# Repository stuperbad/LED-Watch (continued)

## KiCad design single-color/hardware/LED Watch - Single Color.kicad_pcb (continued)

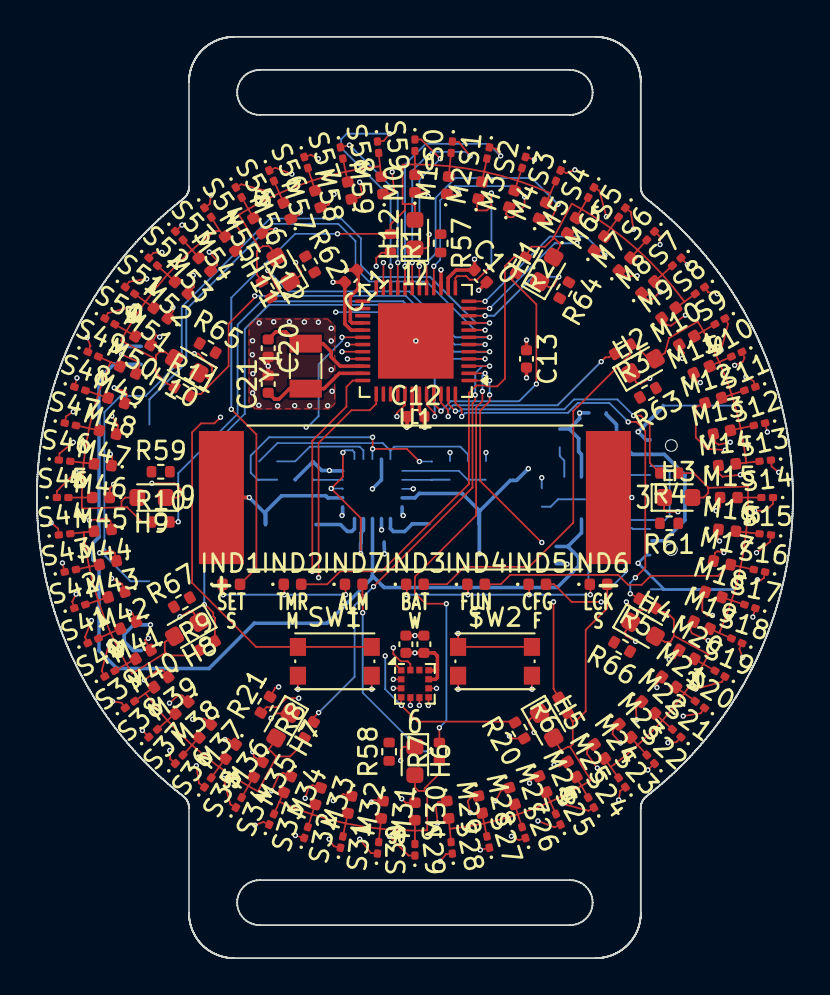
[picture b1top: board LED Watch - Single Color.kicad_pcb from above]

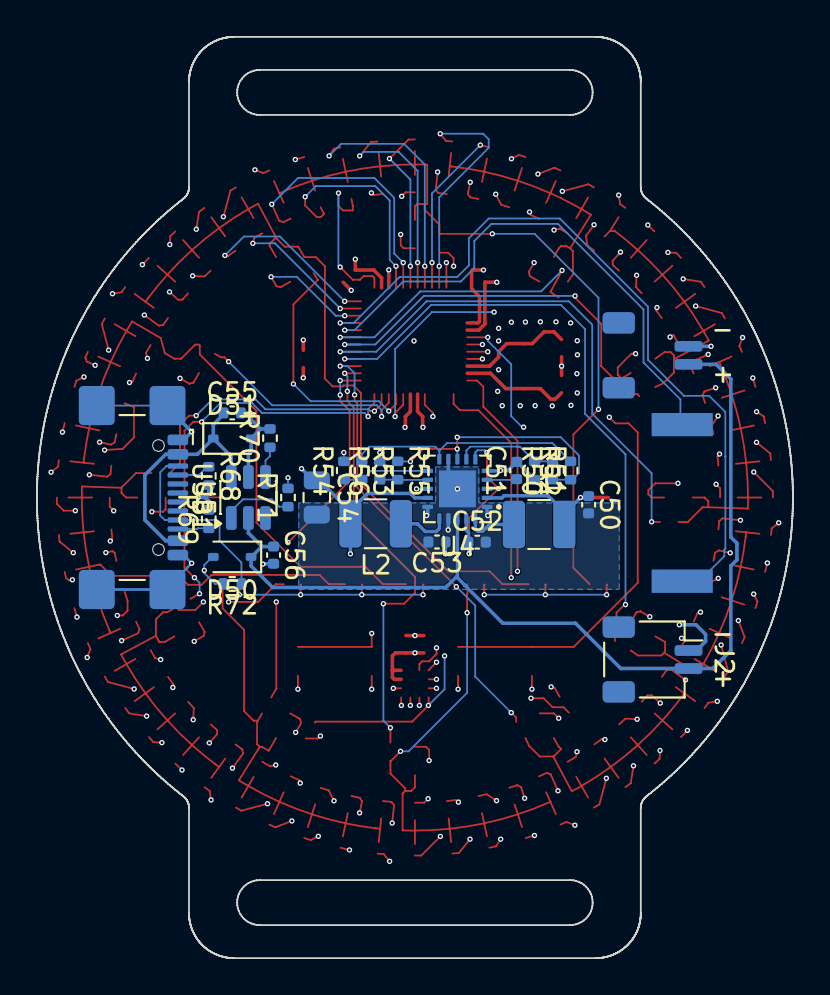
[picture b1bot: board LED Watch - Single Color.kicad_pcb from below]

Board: 4 copper layers, 42.0 x 51.2 mm, 208 parts (31 on the bottom side), 66 nets.

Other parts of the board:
MECH2: LiPo 501515 15x15x5 mm (upper); MECH_LiPo_501515_15x15x5mm
MECH3: LiPo 501515 15x15x5 mm (lower); MECH_LiPo_501515_15x15x5mm

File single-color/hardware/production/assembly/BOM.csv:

Comment,Designator,Footprint,LCSC Part #
PKMCS0909E4000-R1,BZ1,Piezo_Murata_PKMCS0909E4000-R1_9x9mm,C910763
4u7,"C50,C52",C_0402_1005Metric,C23733
10n,"C51,C53",C_0402_1005Metric,C15195
22u,C54,C_0805_2012Metric,C109314
1u,"C55,C56",C_0402_1005Metric,C52923
BAT54WS,D50,D_SOD-323,C304155
UDD32C05L01,D51,D_SOD-323,C19185929
LiPo,"J1,J1B",JST_SH_SM02B-SRSS-TB_1x02-1MP_P1.00mm_Horizontal,C160402
USB-C power + UPDI (GCT USB4110),J2,USB_C_Receptacle_GCT_USB4110,C5143397
22uH,L1,L_1210_3225Metric,C90320
10uH,L2,L_1210_3225Metric,C74563
6.49M,"R50,R53",R_0402_1005Metric,C172111
5.11M,R51,R_0402_1005Metric,C166448
1.47M,R52,R_0402_1005Metric,C477211
3.74M,R54,R_0402_1005Metric,C477705
7.32M,R55,R_0402_1005Metric,C423137
4.22M,R56,R_0402_1005Metric,C423173
5.1k,"R68,R69",R_0402_1005Metric,C25905
10k,"R20,R21,R57,R58,R59,R61,R62,R63,R64,R65,R66,R67,R70,R71",R_0402_1005Metric,C25744
1k,R72,R_0402_1005Metric,C11702
BQ25570RGRR,U4,BQ25570RGR_VQFN-20_3.5x3.5mm_P0.5mm_EP2.05mm,C506250
BQ21040DBV,U5,SOT-23-6,C202311
100n,"C10,C11,C12,C30,C31",C_0402_1005Metric,C1525
10u,C13,C_0402_1005Metric,C15525
18p,"C20,C21",C_0402_1005Metric,C106202
LED white 0603,"H1,H10,H11,H12,H2,H3,H4,H5,H6,H7,H8,H9",LED_0603_1608Metric,C2290
LED white 0402,"IND1,IND2,IND3,IND4,IND5,IND6,IND7,M0,M1,M10,M11,M12,M13,M14,M15,M16,M17,M18,M19,M2,M20,M21,M22,M23,M24,M25,M26,M27,M28,M29,M3,M30,M31,M32,M33,M34,M35,M36,M37,M38,M39,M4,M40,M41,M42,M43,M44,M45,M46,M47,M48,M49,M5,M50,M51,M52,M53,M54,M55,M56,M57,M58,M59,M6,M7,M8,M9",LED_0402_1005Metric,C20613596
220,"R1,R10,R11,R12,R2,R3,R4,R5,R6,R7,R8,R9",R_0402_1005Metric,C25091
LED white 0201,"S0,S1,S10,S11,S12,S13,S14,S15,S16,S17,S18,S19,S2,S20,S21,S22,S23,S24,S25,S26,S27,S28,S29,S3,S30,S31,S32,S33,S34,S35,S36,S37,S38,S39,S4,S40,S41,S42,S43,S44,S45,S46,S47,S48,S49,S5,S50,S51,S52,S53,S54,S55,S56,S57,S58,S59,S6,S7,S8,S9",LED_0201_0603Metric,C965789
SW_Push,"SW1,SW2",SW_Push_1P1T_NO_CK_KMR2,C72443
AVR128DB48-I/6LX,U1,QFN-48-1EP_6x6mm_P0.4mm_EP4.2x4.2mm,C1019768
LIS2DW12TR,U2,LGA-12_2x2mm_P0.5mm,C189624
32.768kHz,Y1,Crystal_SMD_3215-2Pin_3.2x1.5mm,C97606

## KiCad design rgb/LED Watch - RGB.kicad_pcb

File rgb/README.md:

# LED Watch - RGB

The RGB watch: 132 RGB LEDs on three rings plus 7 RGB mode lights, JLCPCB-assemblable parts, AVR128DB64, solar harvester, two LiPo cells, buzzer, accelerometer and buttons. **Status (2026-10-15): placement sketch only**, no schematic, nothing routed. Open **`LED Watch - RGB.kicad_pro`** (it opens the board; the ring LED pads carry the row and colour nets, nothing else has nets yet).

Read **`docs/DESIGN-SKETCH.md`** first: board size, what goes where, the LED choice and its brightness warning, how the matrix is driven, risks and next steps.

| File / folder | What it is |
|---|---|
| `LED Watch - RGB.kicad_pro` / `.kicad_pcb` | the sketch: 44 mm round board with strap lugs, 132 + 7 LEDs, everything placed on the front and back |
| `docs/` | `DESIGN-SKETCH.md`, `pin-plan.csv` (AVR128DB64 pins), `BOM-candidates.csv` (new parts with LCSC numbers and stock, 2026-10-15) |
| `footprints/LEDWatchRGB.pretty` | the new common-anode LED footprint (fits Nationstar NCD0808RGB1 and Meihua MHPA0808RGBDT) |
| `data/` | `led_matrix.csv` (which LED is which second/minute/hour, row and column), `old_ring.json` (ring data read from the old board) |
| `tools/` | `build_sketch.py` makes the board (KiCad's Python: `"C:\Program Files\KiCad.0in\python.exe" toolsuild_sketch.py`), `extract_old_ring.py`, `check_pad_corners.py` |
| `renders/` | `top.png` (front) and `bottom.png` (back, seen from behind) |
| `mechanical/` | watch outline drawings (SVG), the 3D print and the Rhino layout, all of the **old 43 mm board**; not yet updated |
| `archive/` | **`2026-10-14 old RGB board - routed, Harvatek LEDs, ATmega165PA/`**: the previous RGB project (schematic, fully routed board, project, its Gerbers and the October 2026 fab quote work incl. `OPEN-ISSUES.md` and `jlc-alternatives.md`, and the ring placement script); everything older is in `pre-claude/` |

Below: Evan's original notes (part links and ideas).

---

# LED-Watch
first schematic progress commit. adding RGB sketch schematic as well as
completed single LED ring sketch. need to add buttons and sort out AND
gates in the RGB sketch.
Product Ideas.. data sheets and store locations:

Digikey working parts list: https://www.digikey.com/en/mylists/list/WPRJ7CQ35H

Boards options 

27 i/o pins and in the current sketch: https://www.digikey.com/en/products/detail/microchip-technology/ATMEGA4808-MUR/10444956

32 i/o pins: https://www.digikey.com/en/products/detail/microchip-technology/ATMEGA1284P-MU/1914520

LEDs options

addressable 1mm RGB: 
https://www.sparkfun.com/smd-led-addressable-rgb-apa-104-1010-pack-of-20.html
datasheet: https://cdn.sparkfun.com/assets/3/c/c/0/9/SparkFun_APA-104-1010__5mA__LED_Datasheet.pdf

nonaddressable 1mm RGB: 
https://www.digikey.com/en/products/detail/harvatek-corporation/B36J3RGB-F6C0001H4U1930/13588748

discrete white 0603:
https://www.digikey.com/en/products/detail/everlight-electronics-co-ltd/CSP0603AN101-WP30300563001-3T/15286660?s=N4IgjCBcoMwOxVAYygMwIYBsDOBTANCAPZQDaIALAExgAMAHLSALqEAOALlCAMocBOASwB2AcxABfQhQBsiECkgYcBYmRAy4tWgFYYLdl0i8BI8RKkgq6gASZcAExYSgA

Button Options

19 cent 3.4mm square: https://www.digikey.com/en/products/detail/same-sky-formerly-cui-devices/TS21-34-035-BK-260-SMT-TR/21186457

8 cent 5.2mm square: https://www.digikey.com/en/products/detail/c-k/G01008829/16500348

Battery Parts:

Lipo Connector 
Thru-hole - 2mm.. they make 1mm mb? 
https://www.digikey.com/en/products/detail/jst-sales-america-inc/B2B-PH-K-S/926611

Coin Cell Harness
20mm dia. 3.
Do i need a negative connector? is SMD okay?
https://www.digikey.com/en/products/detail/keystone-electronics/3034TR/4499408

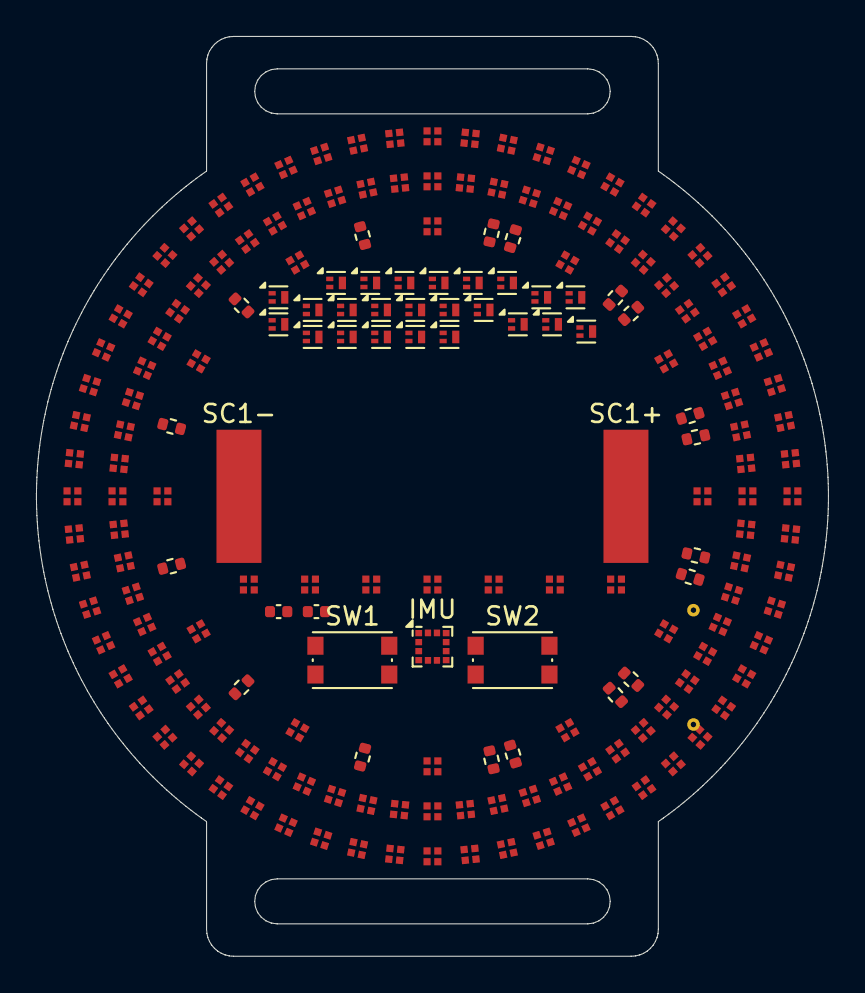
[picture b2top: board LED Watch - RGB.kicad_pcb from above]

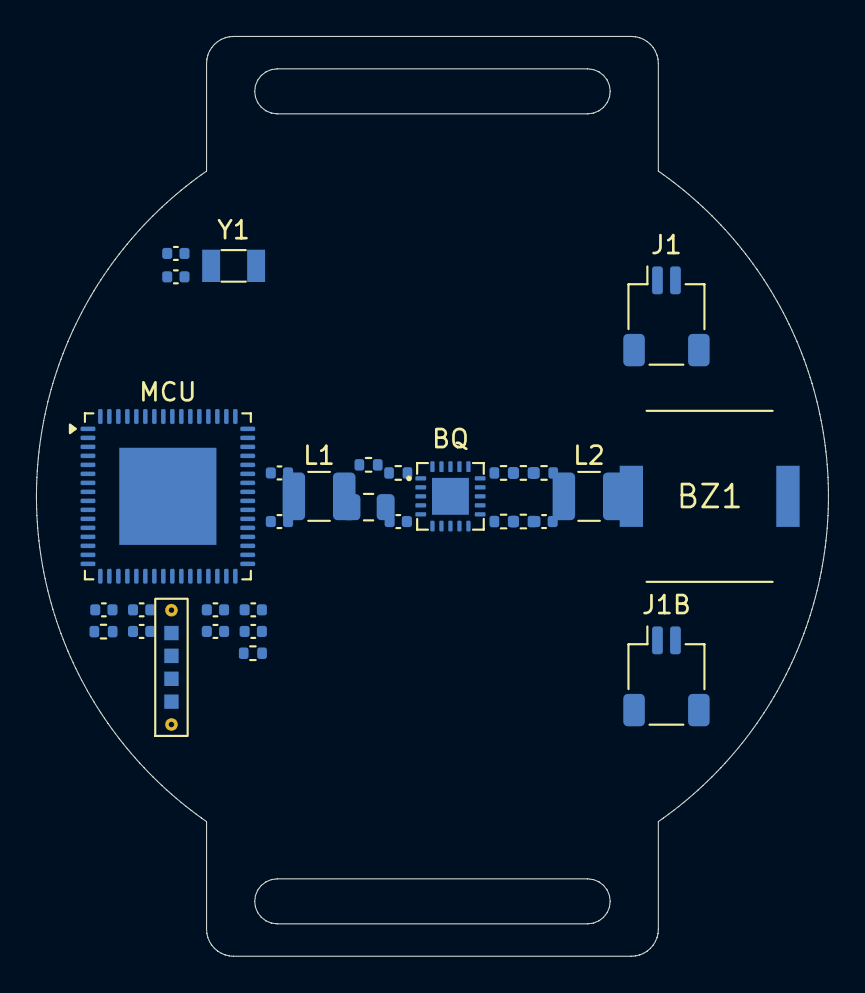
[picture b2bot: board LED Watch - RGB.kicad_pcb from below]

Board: 4 copper layers, 44.0 x 51.1 mm, 220 parts (32 on the bottom side), 40 nets, no tracks yet.

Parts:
BQ: BQ25570; BQ25570RGR_VQFN-20_3.5x3.5mm_P0.5mm_EP2.05mm
BZ1: PKMCS0909E4000-R1; Piezo_Murata_PKMCS0909E4000-R1_9x9mm
C20, C21: 18p; C_0402_1005Metric
C30, C31: 100n; C_0402_1005Metric
C50, C52: 4u7; C_0402_1005Metric
C51, C53: 10n; C_0402_1005Metric
C54: 22u; C_0805_2012Metric
CM1, CM2, CM3, CM4, CM5, CM6, CM7: 100n; C_0402_1005Metric
IMU: LIS2DW12; LGA-12_2x2mm_P0.5mm
IND1, IND2, IND3, IND4, IND5, IND6, IND7: NCD0808RGB1 / MHPA0808RGBDT; RGB0808_CommonAnode
J1, J1B: LiPo; JST_SH_SM02B-SRSS-TB_1x02-1MP_P1.00mm_Horizontal
J2: UPDI pogo; UPDI_Pogo_1x4_P1.27mm_2Guide
L1: 22uH; L_1210_3225Metric
L2: 10uH; L_1210_3225Metric
MCU: AVR128DB64-I/MR; VQFN-64-1EP_9x9mm_P0.5mm_EP5.4x5.4mm
Q1, Q2, Q3, Q4, Q5, Q6, Q7, Q8, Q9, Q10, Q11, Q12, Q13, Q14, Q15, Q16, Q17, Q18, Q19, Q20, Q21, Q22, Q23, Q24: DMP21D0UFB4; Diodes_DFN1006-3
R20, R21: 10k; R_0402_1005Metric
R50, R53, R55: 6.49M; R_0402_1005Metric
R51: 5.11M; R_0402_1005Metric
R52: 1.47M; R_0402_1005Metric
R54, R56: 3.74M; R_0402_1005Metric
RC1, RC2, RC3, RC4, RC5, RC6, RC7, RC8, RC9, RC10, RC11, RC12, RC13, RC14, RC15, RC16, RC17, RC18: R; R_0402_1005Metric
SC1+, SC1-: cell pad; KXOB25_cell_pad_2.5x7.4mm
SW1, SW2: SW; SW_Push_1P1T_NO_CK_KMR2
U2, U3, U4, U5, U6, U7, U8, U9, U10, U11, U12, U13, U14, U15, U16, U17, U18, U19, U20, U21, U22, U23, U24, U25, U26, U27, U28, U29, U30, U31, U32, U33, U34, U35, U36, U37, U38, U39, U40, U41, U42, U43, U44, U45, U46, U47, U48, U49, U50, U51, U52, U53, U54, U55, U56, U57, U58, U59, U60, U61, U62, U63, U64, U65, U66, U67, U68, U69, U70, U71, U72, U73, U74, U75, U76, U77, U78, U79, U80, U81, U82, U83, U84, U85, U86, U87, U88, U89, U90, U91, U92, U93, U94, U95, U96, U97, U98, U99, U100, U101, U102, U103, U104, U105, U106, U107, U108, U109, U110, U111, U112, U113, U114, U115, U116, U117, U118, U119, U120, U121, U122, U123, U124, U125, U126, U127, U128, U129, U130, U131, U132, U133: NCD0808RGB1 / MHPA0808RGBDT; RGB0808_CommonAnode
Y1: 32.768kHz; Crystal_SMD_3215-2Pin_3.2x1.5mm

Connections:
/B1: U2.4, U8.4, U14.4, U20.4, U26.4, U32.4, U38.4, U44.4, U50.4, U56.4, U62.4, U68.4, U74.4, U80.4, U86.4, U92.4, U98.4, U104.4, U110.4, U116.4, U122.4, U128.4
/B2: U3.4, U9.4, U15.4, U21.4, U27.4, U33.4, U39.4, U45.4, U51.4, U57.4, U63.4, U69.4, U75.4, U81.4, U87.4, U93.4, U99.4, U105.4, U111.4, U117.4, U123.4, U129.4
/B3: U4.4, U10.4, U16.4, U22.4, U28.4, U34.4, U40.4, U46.4, U52.4, U58.4, U64.4, U70.4, U76.4, U82.4, U88.4, U94.4, U100.4, U106.4, U112.4, U118.4, U124.4, U130.4
/B4: U5.4, U11.4, U17.4, U23.4, U29.4, U35.4, U41.4, U47.4, U53.4, U59.4, U65.4, U71.4, U77.4, U83.4, U89.4, U95.4, U101.4, U107.4, U113.4, U119.4, U125.4, U131.4
/B5: U6.4, U12.4, U18.4, U24.4, U30.4, U36.4, U42.4, U48.4, U54.4, U60.4, U66.4, U72.4, U78.4, U84.4, U90.4, U96.4, U102.4, U108.4, U114.4, U120.4, U126.4, U132.4
/B6: U7.4, U13.4, U19.4, U25.4, U31.4, U37.4, U43.4, U49.4, U55.4, U61.4, U67.4, U73.4, U79.4, U85.4, U91.4, U97.4, U103.4, U109.4, U115.4, U121.4, U127.4, U133.4
/G1: U2.3, U8.3, U14.3, U20.3, U26.3, U32.3, U38.3, U44.3, U50.3, U56.3, U62.3, U68.3, U74.3, U80.3, U86.3, U92.3, U98.3, U104.3, U110.3, U116.3, U122.3, U128.3
/G2: U3.3, U9.3, U15.3, U21.3, U27.3, U33.3, U39.3, U45.3, U51.3, U57.3, U63.3, U69.3, U75.3, U81.3, U87.3, U93.3, U99.3, U105.3, U111.3, U117.3, U123.3, U129.3
/G3: U4.3, U10.3, U16.3, U22.3, U28.3, U34.3, U40.3, U46.3, U52.3, U58.3, U64.3, U70.3, U76.3, U82.3, U88.3, U94.3, U100.3, U106.3, U112.3, U118.3, U124.3, U130.3
/G4: U5.3, U11.3, U17.3, U23.3, U29.3, U35.3, U41.3, U47.3, U53.3, U59.3, U65.3, U71.3, U77.3, U83.3, U89.3, U95.3, U101.3, U107.3, U113.3, U119.3, U125.3, U131.3
/G5: U6.3, U12.3, U18.3, U24.3, U30.3, U36.3, U42.3, U48.3, U54.3, U60.3, U66.3, U72.3, U78.3, U84.3, U90.3, U96.3, U102.3, U108.3, U114.3, U120.3, U126.3, U132.3
/G6: U7.3, U13.3, U19.3, U25.3, U31.3, U37.3, U43.3, U49.3, U55.3, U61.3, U67.3, U73.3, U79.3, U85.3, U91.3, U97.3, U103.3, U109.3, U115.3, U121.3, U127.3, U133.3
/Hour1: U2.1, U3.1, U4.1, U5.1, U6.1, U7.1
/Hour2: U8.1, U9.1, U10.1, U11.1, U12.1, U13.1
/Minute1: U14.1, U15.1, U16.1, U17.1, U18.1, U19.1
/Minute2: U20.1, U21.1, U22.1, U23.1, U24.1, U25.1
/Minute3: U26.1, U27.1, U28.1, U29.1, U30.1, U31.1
/Minute4: U32.1, U33.1, U34.1, U35.1, U36.1, U37.1
/Minute5: U38.1, U39.1, U40.1, U41.1, U42.1, U43.1
/Minute6: U44.1, U45.1, U46.1, U47.1, U48.1, U49.1
/Minute7: U50.1, U51.1, U52.1, U53.1, U54.1, U55.1
/Minute8: U56.1, U57.1, U58.1, U59.1, U60.1, U61.1
/Minute9: U62.1, U63.1, U64.1, U65.1, U66.1, U67.1
/Minute10: U68.1, U69.1, U70.1, U71.1, U72.1, U73.1
/R1: U2.2, U8.2, U14.2, U20.2, U26.2, U32.2, U38.2, U44.2, U50.2, U56.2, U62.2, U68.2, U74.2, U80.2, U86.2, U92.2, U98.2, U104.2, U110.2, U116.2, U122.2, U128.2
/R2: U3.2, U9.2, U15.2, U21.2, U27.2, U33.2, U39.2, U45.2, U51.2, U57.2, U63.2, U69.2, U75.2, U81.2, U87.2, U93.2, U99.2, U105.2, U111.2, U117.2, U123.2, U129.2
/R3: U4.2, U10.2, U16.2, U22.2, U28.2, U34.2, U40.2, U46.2, U52.2, U58.2, U64.2, U70.2, U76.2, U82.2, U88.2, U94.2, U100.2, U106.2, U112.2, U118.2, U124.2, U130.2
/R4: U5.2, U11.2, U17.2, U23.2, U29.2, U35.2, U41.2, U47.2, U53.2, U59.2, U65.2, U71.2, U77.2, U83.2, U89.2, U95.2, U101.2, U107.2, U113.2, U119.2, U125.2, U131.2
/R5: U6.2, U12.2, U18.2, U24.2, U30.2, U36.2, U42.2, U48.2, U54.2, U60.2, U66.2, U72.2, U78.2, U84.2, U90.2, U96.2, U102.2, U108.2, U114.2, U120.2, U126.2, U132.2
/R6: U7.2, U13.2, U19.2, U25.2, U31.2, U37.2, U43.2, U49.2, U55.2, U61.2, U67.2, U73.2, U79.2, U85.2, U91.2, U97.2, U103.2, U109.2, U115.2, U121.2, U127.2, U133.2
/Second1: U74.1, U75.1, U76.1, U77.1, U78.1, U79.1
/Second2: U80.1, U81.1, U82.1, U83.1, U84.1, U85.1
/Second3: U86.1, U87.1, U88.1, U89.1, U90.1, U91.1
/Second4: U92.1, U93.1, U94.1, U95.1, U96.1, U97.1
/Second5: U98.1, U99.1, U100.1, U101.1, U102.1, U103.1
/Second6: U104.1, U105.1, U106.1, U107.1, U108.1, U109.1
/Second7: U110.1, U111.1, U112.1, U113.1, U114.1, U115.1
/Second8: U116.1, U117.1, U118.1, U119.1, U120.1, U121.1
/Second9: U122.1, U123.1, U124.1, U125.1, U126.1, U127.1
/Second10: U128.1, U129.1, U130.1, U131.1, U132.1, U133.1

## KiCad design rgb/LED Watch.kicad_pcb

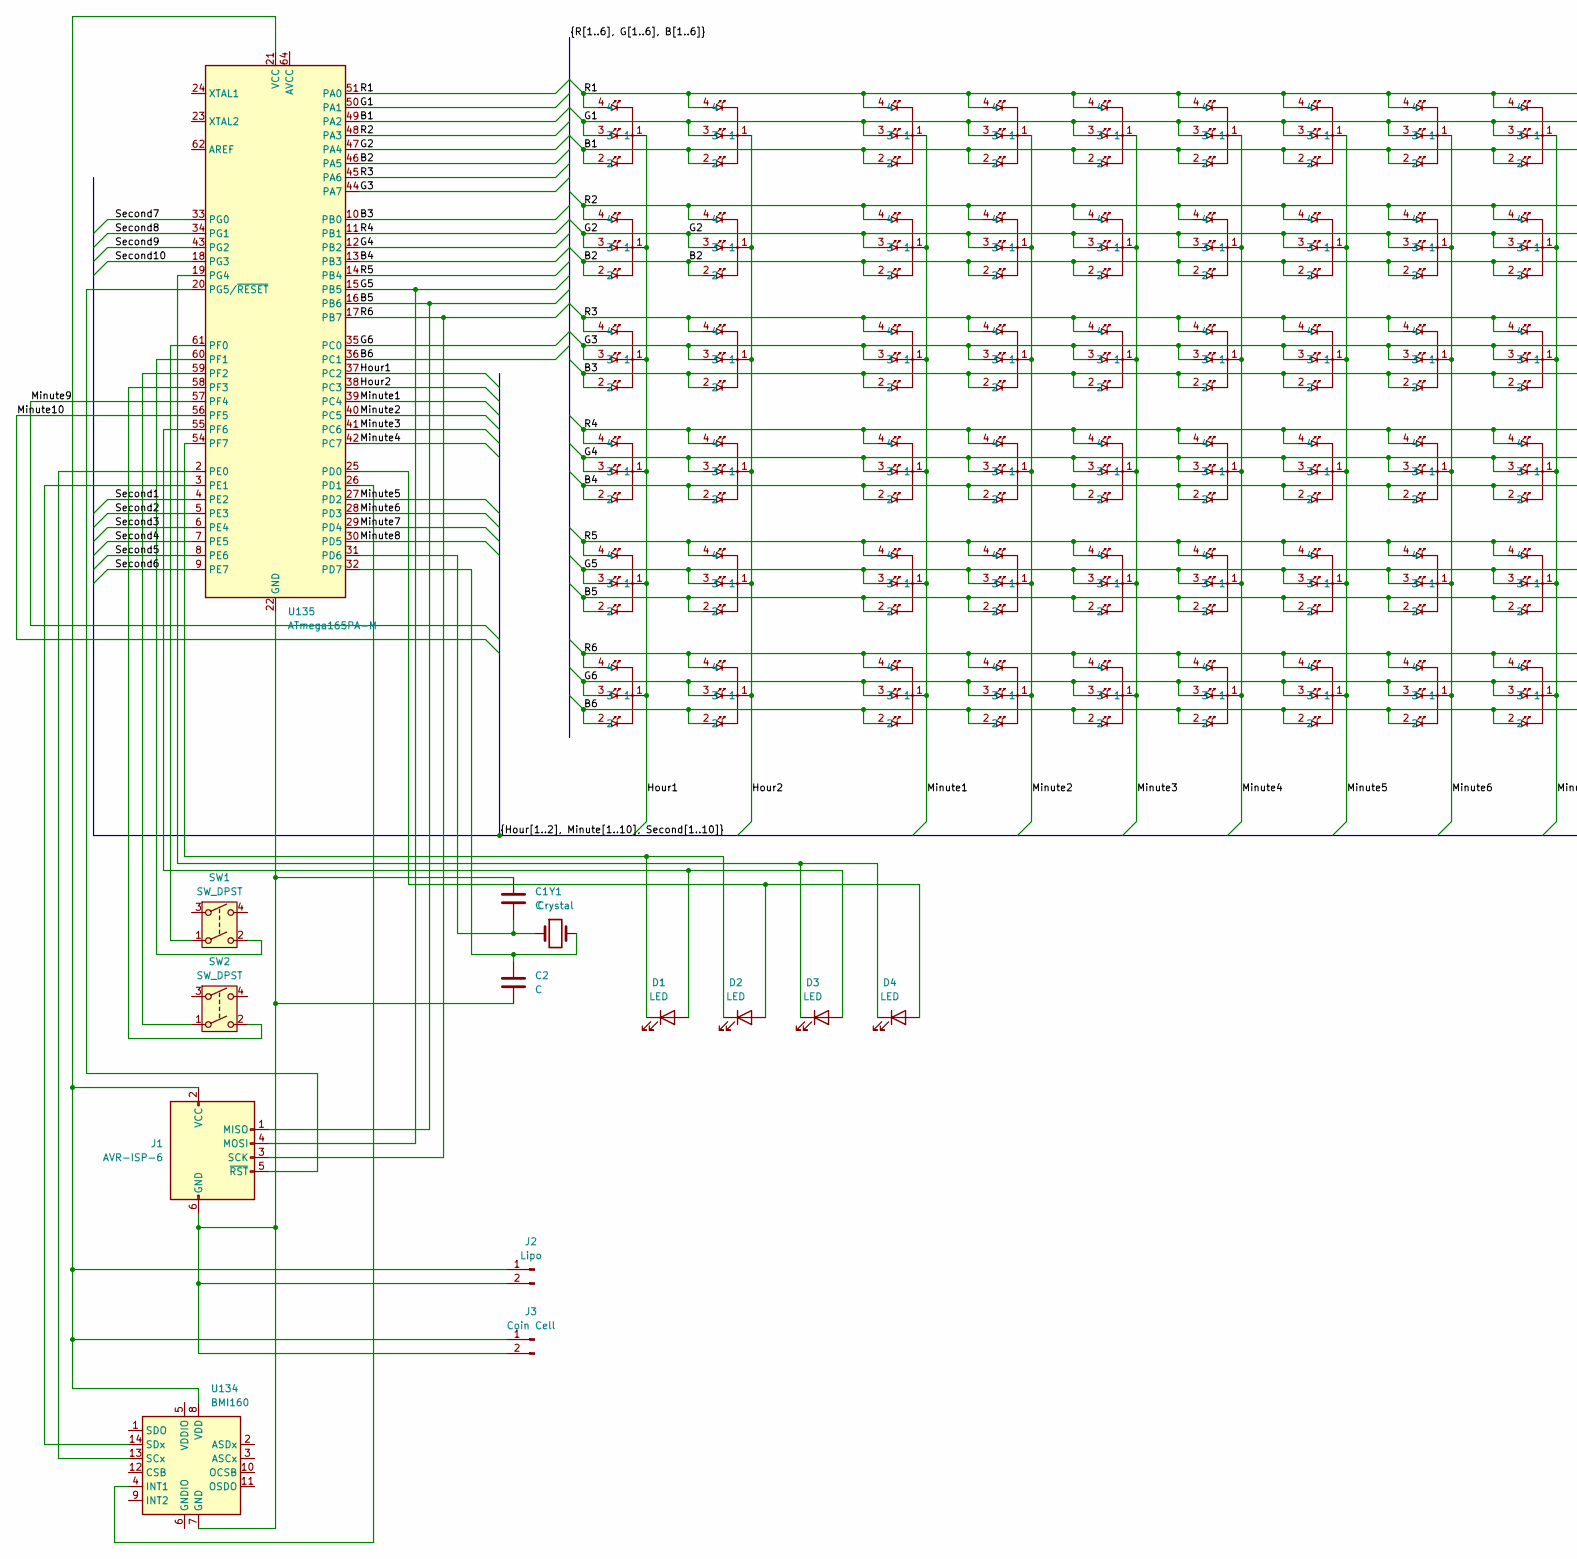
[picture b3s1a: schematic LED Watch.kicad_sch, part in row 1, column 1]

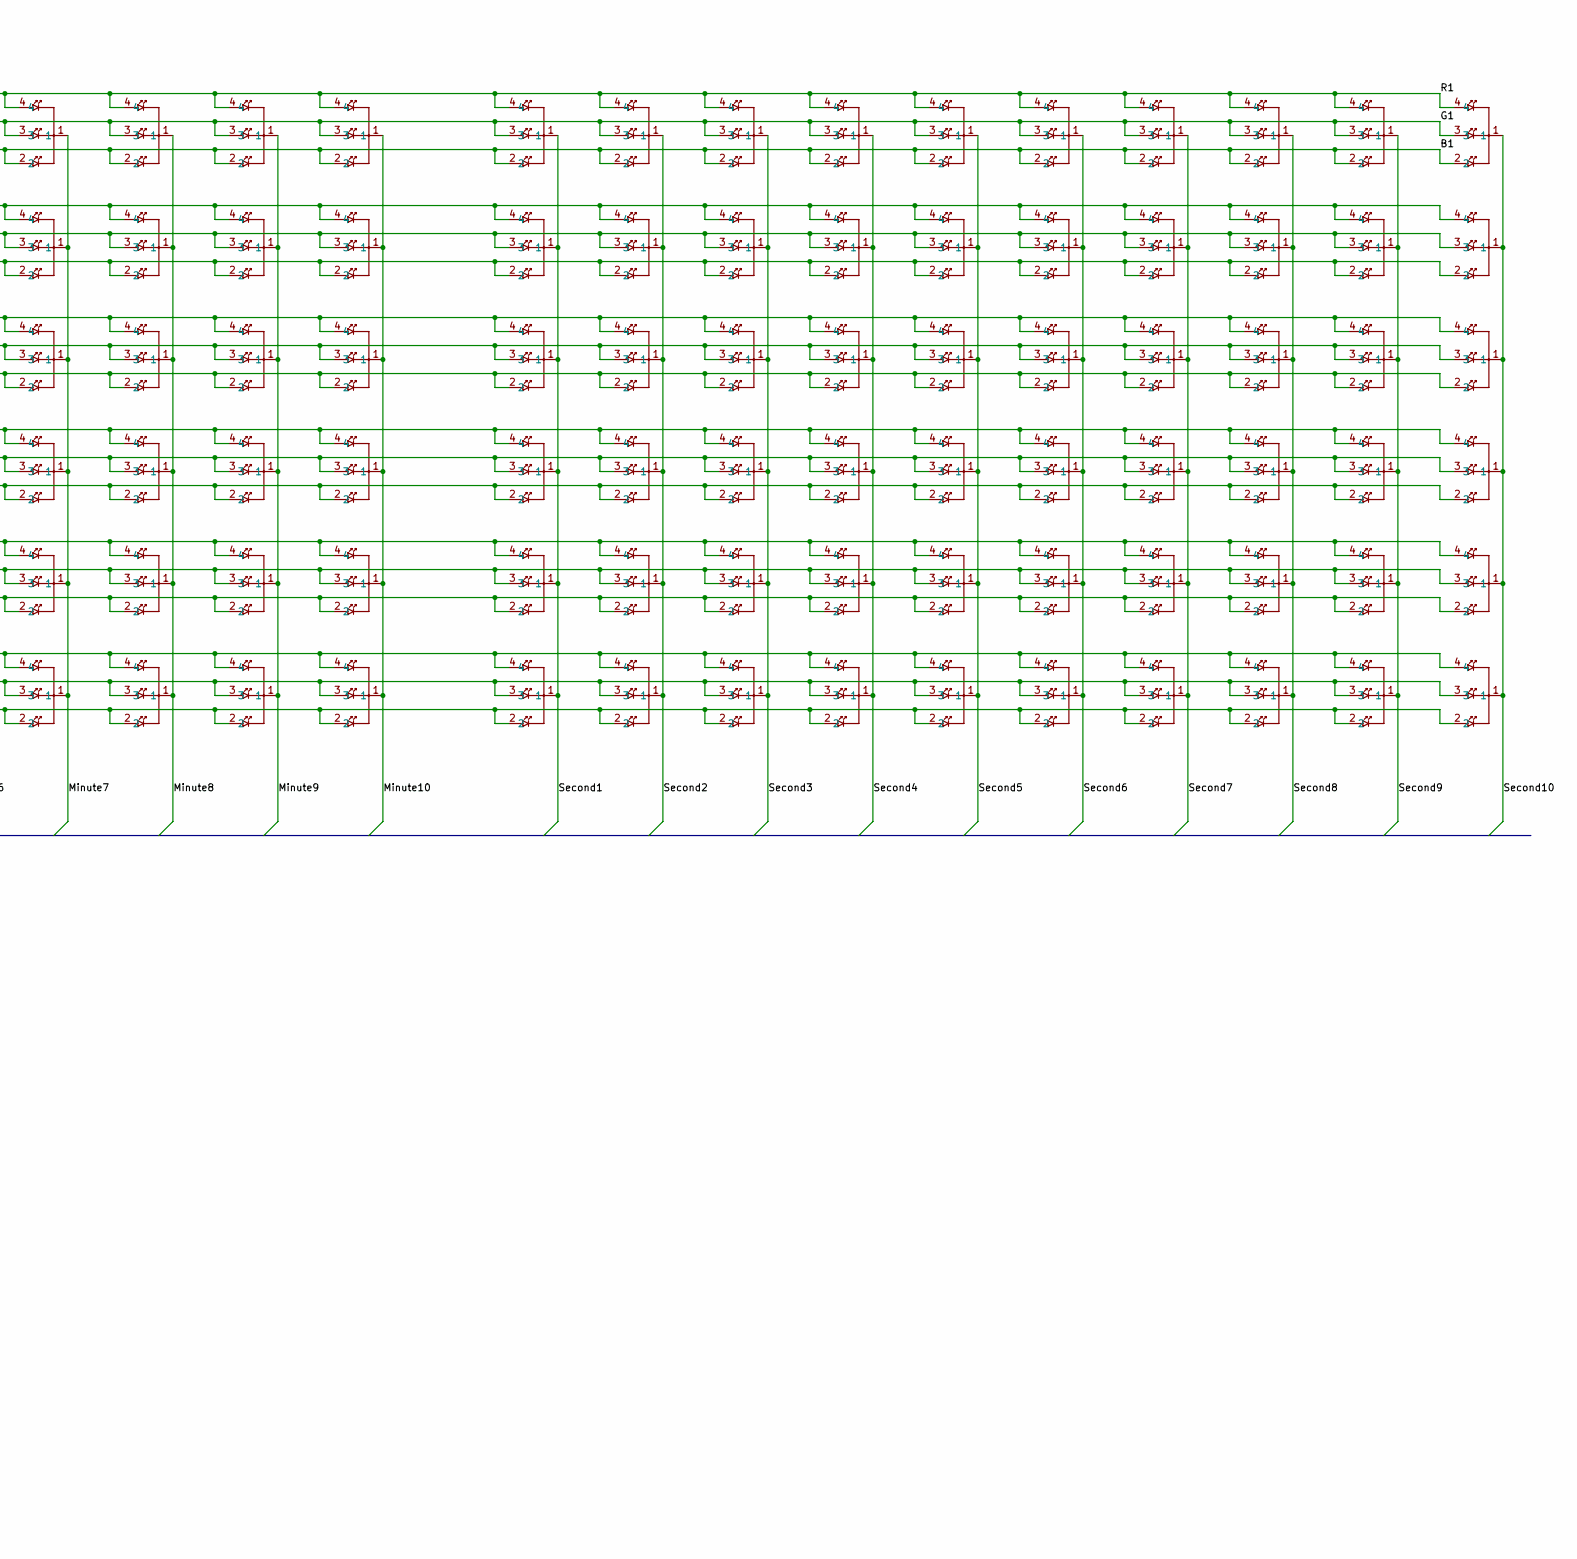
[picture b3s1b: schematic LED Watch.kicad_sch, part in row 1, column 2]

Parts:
C1, C2: C; C_0201_0603Metric
D1, D2, D3, D4: LED; LED_0201_0603Metric
J1: AVR-ISP-6; Tag-Connect_TC2030-IDC-NL_2x03_P1.27mm_Vertical
J2: Lipo; JST_SH_SM02B-SRSS-TB_1x02-1MP_P1.00mm_Horizontal
J3: Coin Cell; BatteryHolder_Keystone_3034_1x20mm
SW1, SW2: SW_DPST; SW_TS21-34-035-BK-260-SMT-TR
U2, U3, U4, U5, U6, U7, U8, U9, U10, U11, U12, U13, U14, U15, U16, U17, U18, U19, U20, U21, U22, U23, U24, U25, U26, U27, U28, U29, U30, U31, U32, U33, U34, U35, U36, U37, U38, U39, U40, U41, U42, U43, U44, U45, U46, U47, U48, U49, U50, U51, U52, U53, U54, U55, U56, U57, U58, U59, U60, U61, U62, U63, U64, U65, U66, U67, U68, U69, U70, U71, U72, U73, U74, U75, U76, U77, U78, U79, U80, U81, U82, U83, U84, U85, U86, U87, U88, U89, U90, U91, U92, U93, U94, U95, U96, U97, U98, U99, U100, U101, U102, U103, U104, U105, U106, U107, U108, U109, U110, U111, U112, U113, U114, U115, U116, U117, U118, U119, U120, U121, U122, U123, U124, U125, U126, U127, U128, U129, U130, U131, U132, U133: B39D3RGB-F6C0001HOU1930; B39D3RGB-F6C0001HOU1930_HVK; MPN LTST-C19HE1WT; Digi-Key_PN 160-2162-1-ND
U134: BMI160; Bosch_LGA-14_3x2.5mm_P0.5mm
U135: ATmega165PA-M; QFN-64-1EP_9x9mm_P0.5mm_EP5.4x5.4mm
Y1: Crystal; Crystal_SMD_3215-2Pin_3.2x1.5mm

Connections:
/B1: U2.2, U8.2, U14.2, U20.2, U26.2, U32.2, U38.2, U44.2, U50.2, U56.2, U62.2, U68.2, U74.2, U80.2, U86.2, U92.2, U98.2, U104.2, U110.2, U116.2, U122.2, U128.2, U135.49 (PA2)
/B2: U3.2, U9.2, U15.2, U21.2, U27.2, U33.2, U39.2, U45.2, U51.2, U57.2, U63.2, U69.2, U75.2, U81.2, U87.2, U93.2, U99.2, U105.2, U111.2, U117.2, U123.2, U129.2, U135.46 (PA5)
/B3: U4.2, U10.2, U16.2, U22.2, U28.2, U34.2, U40.2, U46.2, U52.2, U58.2, U64.2, U70.2, U76.2, U82.2, U88.2, U94.2, U100.2, U106.2, U112.2, U118.2, U124.2, U130.2, U135.10 (PB0)
/B4: U5.2, U11.2, U17.2, U23.2, U29.2, U35.2, U41.2, U47.2, U53.2, U59.2, U65.2, U71.2, U77.2, U83.2, U89.2, U95.2, U101.2, U107.2, U113.2, U119.2, U125.2, U131.2, U135.13 (PB3)
/B5: J1.1 (MISO), U6.2, U12.2, U18.2, U24.2, U30.2, U36.2, U42.2, U48.2, U54.2, U60.2, U66.2, U72.2, U78.2, U84.2, U90.2, U96.2, U102.2, U108.2, U114.2, U120.2, U126.2, U132.2, U135.16 (PB6)
/B6: U7.2, U13.2, U19.2, U25.2, U31.2, U37.2, U43.2, U49.2, U55.2, U61.2, U67.2, U73.2, U79.2, U85.2, U91.2, U97.2, U103.2, U109.2, U115.2, U121.2, U127.2, U133.2, U135.36 (PC1)
/G1: U2.3, U8.3, U14.3, U20.3, U26.3, U32.3, U38.3, U44.3, U50.3, U56.3, U62.3, U68.3, U74.3, U80.3, U86.3, U92.3, U98.3, U104.3, U110.3, U116.3, U122.3, U128.3, U135.50 (PA1)
/G2: U3.3, U9.3, U15.3, U21.3, U27.3, U33.3, U39.3, U45.3, U51.3, U57.3, U63.3, U69.3, U75.3, U81.3, U87.3, U93.3, U99.3, U105.3, U111.3, U117.3, U123.3, U129.3, U135.47 (PA4)
/G3: U4.3, U10.3, U16.3, U22.3, U28.3, U34.3, U40.3, U46.3, U52.3, U58.3, U64.3, U70.3, U76.3, U82.3, U88.3, U94.3, U100.3, U106.3, U112.3, U118.3, U124.3, U130.3, U135.44 (PA7)
/G4: U5.3, U11.3, U17.3, U23.3, U29.3, U35.3, U41.3, U47.3, U53.3, U59.3, U65.3, U71.3, U77.3, U83.3, U89.3, U95.3, U101.3, U107.3, U113.3, U119.3, U125.3, U131.3, U135.12 (PB2)
/G5: J1.4 (MOSI), U6.3, U12.3, U18.3, U24.3, U30.3, U36.3, U42.3, U48.3, U54.3, U60.3, U66.3, U72.3, U78.3, U84.3, U90.3, U96.3, U102.3, U108.3, U114.3, U120.3, U126.3, U132.3, U135.15 (PB5)
/G6: U7.3, U13.3, U19.3, U25.3, U31.3, U37.3, U43.3, U49.3, U55.3, U61.3, U67.3, U73.3, U79.3, U85.3, U91.3, U97.3, U103.3, U109.3, U115.3, U121.3, U127.3, U133.3, U135.35 (PC0)
/Hour1: U2.1, U3.1, U4.1, U5.1, U6.1, U7.1, U135.37 (PC2)
/Hour2: U8.1, U9.1, U10.1, U11.1, U12.1, U13.1, U135.38 (PC3)
/Minute1: U14.1, U15.1, U16.1, U17.1, U18.1, U19.1, U135.39 (PC4)
/Minute2: U20.1, U21.1, U22.1, U23.1, U24.1, U25.1, U135.40 (PC5)
/Minute3: U26.1, U27.1, U28.1, U29.1, U30.1, U31.1, U135.41 (PC6)
/Minute4: U32.1, U33.1, U34.1, U35.1, U36.1, U37.1, U135.42 (PC7)
/Minute5: U38.1, U39.1, U40.1, U41.1, U42.1, U43.1, U135.27 (PD2)
/Minute6: U44.1, U45.1, U46.1, U47.1, U48.1, U49.1, U135.28 (PD3)
/Minute7: U50.1, U51.1, U52.1, U53.1, U54.1, U55.1, U135.29 (PD4)
/Minute8: U56.1, U57.1, U58.1, U59.1, U60.1, U61.1, U135.30 (PD5)
/Minute9: U62.1, U63.1, U64.1, U65.1, U66.1, U67.1, U135.57 (PF4)
/Minute10: U68.1, U69.1, U70.1, U71.1, U72.1, U73.1, U135.56 (PF5)
/R1: U2.4, U8.4, U14.4, U20.4, U26.4, U32.4, U38.4, U44.4, U50.4, U56.4, U62.4, U68.4, U74.4, U80.4, U86.4, U92.4, U98.4, U104.4, U110.4, U116.4, U122.4, U128.4, U135.51 (PA0)
/R2: U3.4, U9.4, U15.4, U21.4, U27.4, U33.4, U39.4, U45.4, U51.4, U57.4, U63.4, U69.4, U75.4, U81.4, U87.4, U93.4, U99.4, U105.4, U111.4, U117.4, U123.4, U129.4, U135.48 (PA3)
/R3: U4.4, U10.4, U16.4, U22.4, U28.4, U34.4, U40.4, U46.4, U52.4, U58.4, U64.4, U70.4, U76.4, U82.4, U88.4, U94.4, U100.4, U106.4, U112.4, U118.4, U124.4, U130.4, U135.45 (PA6)
/R4: U5.4, U11.4, U17.4, U23.4, U29.4, U35.4, U41.4, U47.4, U53.4, U59.4, U65.4, U71.4, U77.4, U83.4, U89.4, U95.4, U101.4, U107.4, U113.4, U119.4, U125.4, U131.4, U135.11 (PB1)
/R5: U6.4, U12.4, U18.4, U24.4, U30.4, U36.4, U42.4, U48.4, U54.4, U60.4, U66.4, U72.4, U78.4, U84.4, U90.4, U96.4, U102.4, U108.4, U114.4, U120.4, U126.4, U132.4, U135.14 (PB4)
/R6: J1.3 (SCK), U7.4, U13.4, U19.4, U25.4, U31.4, U37.4, U43.4, U49.4, U55.4, U61.4, U67.4, U73.4, U79.4, U85.4, U91.4, U97.4, U103.4, U109.4, U115.4, U121.4, U127.4, U133.4, U135.17 (PB7)
/Second1: U74.1, U75.1, U76.1, U77.1, U78.1, U79.1, U135.4 (PE2)
/Second2: U80.1, U81.1, U82.1, U83.1, U84.1, U85.1, U135.5 (PE3)
/Second3: U86.1, U87.1, U88.1, U89.1, U90.1, U91.1, U135.6 (PE4)
/Second4: U92.1, U93.1, U94.1, U95.1, U96.1, U97.1, U135.7 (PE5)
/Second5: U98.1, U99.1, U100.1, U101.1, U102.1, U103.1, U135.8 (PE6)
/Second6: U104.1, U105.1, U106.1, U107.1, U108.1, U109.1, U135.9 (PE7)
/Second7: U110.1, U111.1, U112.1, U113.1, U114.1, U115.1, U135.33 (PG0)
/Second8: U116.1, U117.1, U118.1, U119.1, U120.1, U121.1, U135.34 (PG1)
/Second9: U122.1, U123.1, U124.1, U125.1, U126.1, U127.1, U135.43 (PG2)
/Second10: U128.1, U129.1, U130.1, U131.1, U132.1, U133.1, U135.18 (PG3)
unnamed: D1.2 (A), D3.2 (A), U135.55 (PF6)
unnamed: D1.1 (K), D2.1 (K), U135.54 (PF7)
unnamed: D2.2 (A), D4.2 (A), U135.25 (PD0)
unnamed: D3.1 (K), D4.1 (K), U135.19 (PG4)
unnamed: C1.1, C2.2, J1.6 (GND), J2.2, J3.2, U134.7 (GND), U135.22 (GND), U135.53 (GND), U135.63 (GND), U135.65 (GND)
unnamed: J1.2 (VCC), J2.1, J3.1, U134.8 (VDD), U135.21 (VCC), U135.52 (VCC)
unnamed: J1.5 (~RST), U135.20 (PG5/~RESET)
unnamed: U134.4 (INT1), U135.26 (PD1)
unnamed: U134.13 (SCx), U135.2 (PE0)
unnamed: U134.14 (SDx), U135.3 (PE1)
unnamed: C1.2, U135.31 (PD6), Y1.1
unnamed: C2.1, U135.32 (PD7), Y1.2
unnamed: SW1.1, U135.61 (PF0)
unnamed: SW1.2, U135.60 (PF1)
unnamed: SW2.1, U135.59 (PF2)
unnamed: SW2.2, U135.58 (PF3)

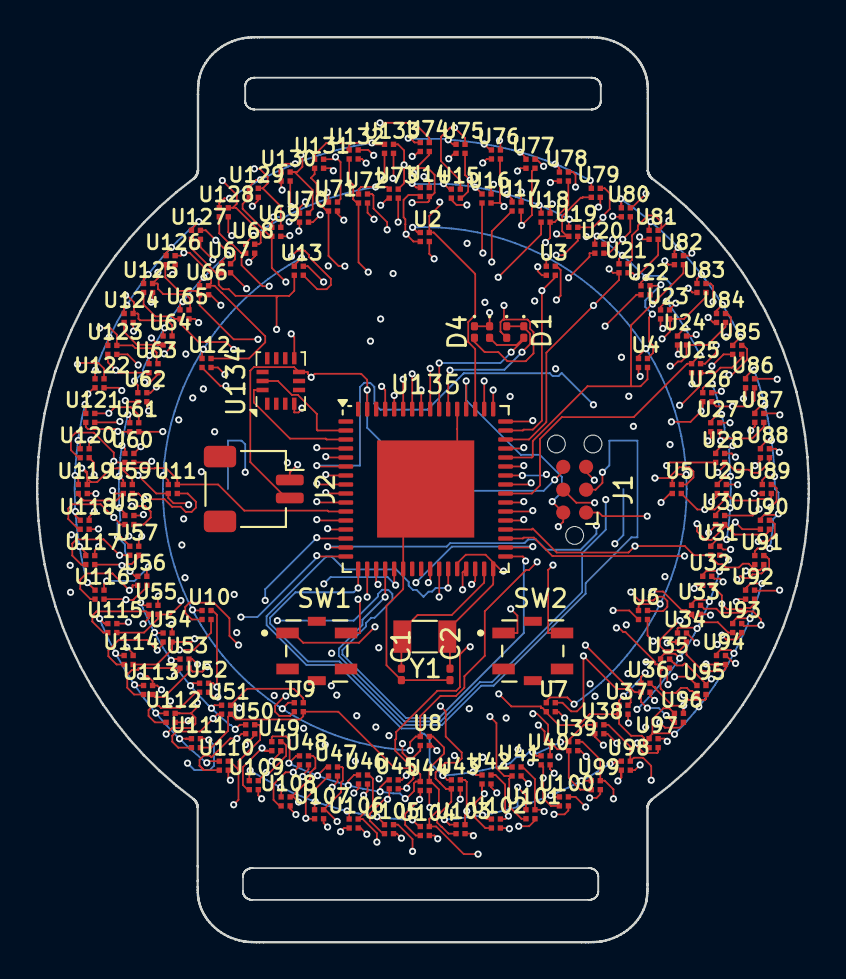
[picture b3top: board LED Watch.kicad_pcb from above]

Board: 4 copper layers, 42.9 x 50.3 mm, 146 parts (1 on the bottom side), 56 nets.

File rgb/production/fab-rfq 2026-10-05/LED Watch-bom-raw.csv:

"Reference","Value","Footprint","QUANTITY"
"C1,C2","C","Capacitor_SMD:C_0201_0603Metric","2"
"D1-D4","LED","LED_SMD:LED_0201_0603Metric","4"
"J1","AVR-ISP-6","Connector:Tag-Connect_TC2030-IDC-NL_2x03_P1.27mm_Vertical","1"
"J2","Lipo","Connector_JST:JST_SH_SM02B-SRSS-TB_1x02-1MP_P1.00mm_Horizontal","1"
"J3","Coin Cell","Battery:BatteryHolder_Keystone_3034_1x20mm","1"
"SW1,SW2","SW_DPST","kicad-footprints:SW_TS21-34-035-BK-260-SMT-TR","2"
"U2-U133","B39D3RGB-F6C0001HOU1930","B39D3RGB_F6C0001HOU1930:B39D3RGB-F6C0001HOU1930_HVK","132"
"U134","BMI160","Package_LGA:Bosch_LGA-14_3x2.5mm_P0.5mm","1"
"U135","ATmega165PA-M","Package_DFN_QFN:QFN-64-1EP_9x9mm_P0.5mm_EP5.4x5.4mm","1"
"Y1","Crystal","Crystal:Crystal_SMD_3215-2Pin_3.2x1.5mm","1"

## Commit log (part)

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2025-09-09 adding kicad files
2025-09-16 first schematic progress commit. adding RGB sketch schematic as well as completed single LED ring sketch. need to add buttons and sort out AND gates in the RGB sketch.
2025-09-16 adds some readme text
2025-09-16 chip swap to atmega4808
2025-09-16 small edits
2025-10-13 added bus bars. things are where i think they should be but i need to double check transistors and do a lot more
2025-10-29 making sure all up to date
2025-11-18 added AVR 6 pin header, 2 buttons, lipo and coincell connectors, and idk.. stuff.. ready for pathing soon hopefully.
2025-11-18 adjusted clocking and spacings.. ready for routing
2025-11-19 Update README: target MCU and KiCad hardware info
2025-11-21 adjusted clocking and spacings.. ready for routing again
2025-11-22 added caps.. still unsuccessful routing
2025-11-25 traced out? iteration 1 at least.. passes an initial drc run.. I want to add a couple test regular white leds.. i should source and add for testing of potential single color board
2025-11-25 traced out, just a few minor cleanups.
2025-12-04 pulled vias from under chip and added 4 0603 pads for testing options
2025-12-13 not sure, not much changed.. but updated w/ gerber for order
